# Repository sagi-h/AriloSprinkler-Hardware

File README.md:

# AriloSprinkler-Hardware
OpenSprinkler ESP32-WROOM Hardware Design variant including a Lora E22-900M30S-SX1262 and made in Kicad software.

HW features:
- 8 valve AC driver compatible with OpenSprinkler Zone Expanders
- Lora E22-900M30S-SX1262 long range transceiver (up to 30dBm)
- USB interface for debugging/flashing
- Ethernet interface (Exemplary module: https://de.aliexpress.com/item/2042562851.html?spm=a2g0s.9042311.0.0.27424c4daFHBJU)
- RF Transmitter interface (Exemplary module: https://de.aliexpress.com/item/4001119703303.html?spm=a2g0s.9042311.0.0.27424c4daFHBJU)
- Compatible with DIN rails (Used holding system: https://de.aliexpress.com/item/32827395562.html?spm=a2g0s.9042311.0.0.27424c4daFHBJU)
- Reworked current measurement with inverted precision rectifier required due to the ADC of the ESP32
- RTC
- Button switches

Tested features:
- Opensprinkler SW features work
- Lora transceiver works
- Current measurement works
- Valve control works
- Button switches work

All parts have a LCSC reference number and are at the time of writting this readme available in the JLCPCB SMT library. I have got my prototype boards produced by JLCPCB (quite inexpensive, 5 full SMT assembled and shipped PCB's for arround 75€, additionally E22 module, ESP32 and USB and SMT connectors to be added).

The compatible SW can be found in the following OpenSprinkler Firmware branch:
https://github.com/arijav/AriloSprinkler-Firmware

Note: This is a home made prototype. No guarantee of any kind is given. If you want a commercial product please order the regular OpenSprinkler official parts.

Final design (not yet produced, use at your own risk):

Prototype:

For questions send a message to:
gmail email: arijav2020

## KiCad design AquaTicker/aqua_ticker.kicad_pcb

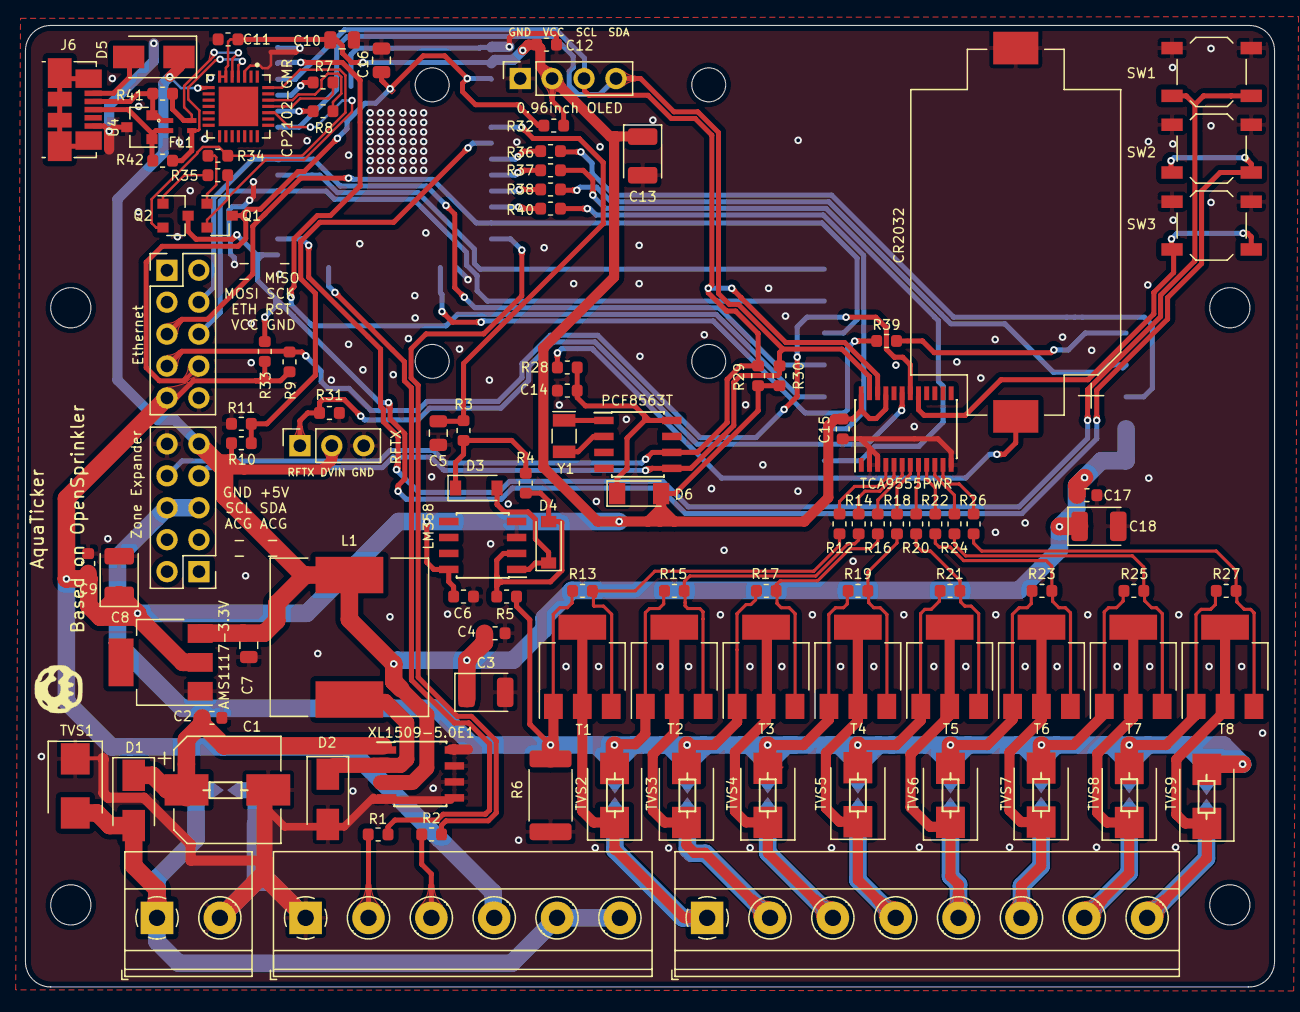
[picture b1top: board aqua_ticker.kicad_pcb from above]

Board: 2 copper layers, 99.4 x 76.5 mm, 118 parts (0 on the bottom side), 80 nets.

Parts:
BT1: CR2032; BatteryHolder_Keystone_1060_1x2032
C1: 100uF; CP_Elec_8x10
C2, C4, C6, C9, C11, C12, C14, C15, C17: 0.1u; C_0603_1608Metric
C3, C8, C13, C18: 100uF; CP_EIA-3528-21_Kemet-B
C5, C7, C10: 10u; C_0805_2012Metric
C16: 1u; C_0805_2012Metric
D1, D5: M7; D_SMA
D2: SS34; D_SMA
D3, D4: DN4148; D_SOD-123
D6: LL4148; D_MiniMELF
FL1: ACM2012-121-2P-T002; FIL_ACM2012-121-2P-T002
J1: M024MM-X; TerminalBlock_Phoenix_MKDS-1,5-2_1x02_P5.00mm_Horizontal
J2: M065MM; TerminalBlock_Phoenix_MKDS-1,5-6_1x06_P5.00mm_Horizontal
J3: RFTX; PinSocket_1x03_P2.54mm_Vertical
J4: Ethernet; PinHeader_2x05_P2.54mm_Vertical
J5: Zone Expander; PinHeader_2x05_P2.54mm_Vertical
J6: USB_B_Micro; USB_Micro-B_Molex_47346-0001
J7: M085MM-8; TerminalBlock_Phoenix_MKDS-1,5-8_1x08_P5.00mm_Horizontal
J8: 0.96inch OLED; PinSocket_1x04_P2.54mm_Vertical
L1: 68uH; L_12x12mm_H6mm
Q1, Q2: Q_NPN_BCE; SOT-23
R1, R2, R34, R35: 4K7; R_0603_1608Metric
R3: 100; R_0603_1608Metric
R4: 300K; R_0603_1608Metric
R5, R10, R11: 100K; R_0603_1608Metric
R6: 0.20; R_2512_6332Metric
R7, R8: 470; R_0603_1608Metric
R9, R28, R32: 10K; R_0603_1608Metric
R12, R14, R16, R18, R20, R22, R24, R26: 390; R_0603_1608Metric
R13, R15, R17, R19, R21, R23, R25, R27: 470K; R_0603_1608Metric
R29, R30, R31, R33: 1K; R_0603_1608Metric
R36, R37, R38, R39, R40: 22R; R_0603_1608Metric
R41, R42: 10; R_0603_1608Metric
SP1, SP2, SP3, SP4, SP5, SP6, SP7, SP8, SP9: PCB-SGAP
SW1, SW2, SW3: SW_SPST; SW_SPST_TL3342
T1, T2, T3, T4, T5, T6, T7, T8: Z0103MN5AA4; SOT-223
TVS1: 43CA; D_SMB
TVS2, TVS3, TVS4, TVS5, TVS6, TVS7, TVS8: SMBJ43CA; D_SMB
TVS9: TVSSMB; D_SMB
U1: XL1509-5.0E1; SOIC-8_3.9x4.9mm_P1.27mm
U2: LM358; SOIC-8_3.9x4.9mm_P1.27mm
U3: AMS1117-3.3V; SOT-223
U4: PSM712-LF-T7; SOT-23
U5: CP2102-GMR; QFN50P500X500X100-29N
U6: ESP32-WROOM-32D; ESP32-WROOM-32
U7: PCF8563T; SOIC-8_3.9x4.9mm_P1.27mm
U8: TCA9555PWR; TSSOP-24_4.4x7.8mm_P0.65mm
U9: E22-900M30S-SX1262
Y1: Crystal_Small; Crystal_SMD_G8-2Pin_3.2x1.5mm

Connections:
/ACRET: J5.5, J5.6, R5.1, R6.1, R13.2, R15.2, R17.2, R19.2, R21.2, R23.2, R25.2, R27.2, SP2.2, SP3.2, SP4.2, SP5.2, SP6.2, SP7.2, SP8.2, SP9.2, T1.1, T2.1, T3.1, T4.1, T5.1, T6.1, T7.1, T8.1, TVS2.2, TVS3.2, TVS4.2, TVS5.2, TVS6.2, TVS7.2, TVS8.2, TVS9.2
/BUSY: R40.2, U9.14
/COM: D1.2, J1.1, J2.5, J2.6, SP1.2, TVS1.2
/D+: FL1.2, J6.3, R42.1, U4.1
/D-: FL1.1, J6.2, R41.2, U4.2
/DADC: C5.1, R3.1, U6.6
/DIO1: R37.2, U9.13
/DIO2: R36.2, U9.8
/DM: FL1.4, R41.1, U5.5
/DP: FL1.3, R42.2, U5.4
/DSCL: J5.8, J8.3, R29.2, U6.36, U7.6, U8.22
/DSDA: J5.7, J8.4, R30.2, U6.33, U7.5, U8.23
/DTR: Q2.2, R34.2, U5.28
/DVIN: C3.1, C4.1, C7.1, C17.1, C18.1, D5.1, J3.2, J5.9, L1.2, R11.1, U1.3, U3.3, U5.8, U9.9, U9.10
/DVINSENS: R10.1, R11.2, U6.7
/ETH: J4.7, R9.2, U8.18
/GPIO0: Q2.3, R33.2, SW2.1, U6.25
/IO13: R39.1, U6.16
/IO25: R38.1, U6.10
/IO26: R40.1, U6.11
/IO32: R36.1, U6.8
/IO33: R37.1, U6.9
/MISO: J4.4, U6.31, U9.16
/MOSI: J4.5, U6.12, U9.17
/NSS_SEL: U6.30, U9.19
/P0: R12.1, U8.4
/P1: R14.1, U8.5
/P2: R16.1, U8.6
/P3: R18.1, U8.7
/P4: R20.1, U8.8
/P5: R22.1, U8.9
/P6: R24.1, U8.10
/P7: R26.1, U8.11
/RESET: U6.37, U9.15
/RFTX: J3.1, R31.1, U8.19
/RST: C16.1, J4.8, Q1.3, R32.1, U6.3
/RTS: Q1.2, R35.2, U5.24
/RXD: R8.2, U6.34
/RXEN: R39.2, U9.6
/SCK: J4.6, U6.29, U9.18
/SENS1: R1.2, U6.23
/SENS2: R2.2, U6.13
/SW1: SW1.1, U6.26
/SW3: SW3.1, U8.17
/TXD: R7.2, U6.35
/TXEN: R38.2, U9.7
/VBUS: D5.2, J6.1
/VCC: C6.1, C8.1, C9.1, C10.1, C11.1, C12.1, C13.1, C15.1, D6.2, J2.4, J4.9, J8.2, R9.1, R29.1, R30.1, R32.2, R33.1, U2.8, U3.2, U5.6, U5.7, U6.2, U8.21, U8.24
GND: BT1.2, C1.2, C2.2, C3.2, C4.2, C5.2, C6.2, C7.2, C8.2, C9.2, C10.2, C11.2, C12.2, C13.2, C14.2, C15.2, C16.2, C17.2, C18.2, D2.2, J1.2, J2.1, J3.3, J4.10, J5.10, J6.5, J8.1, R6.2, R10.2, R31.2, SP1.1, SW1.2, SW2.2, SW3.2, TVS1.1, U1.4, U1.5, U1.6, U1.7, U1.8, U2.3, U2.4, U3.1, U4.3, U5.3, U6.1, U6.15, U6.38, U6.39, U7.4, U8.2, U8.3, U8.12, U9.1, U9.2, U9.3, U9.4, U9.5, U9.11, U9.12, U9.20, U9.22
unnamed: BT1.1, R28.2
unnamed: C1.1, C2.1, D1.1, U1.1
unnamed: C14.1, D6.1, R28.1, U7.8
unnamed: D2.1, L1.1, U1.2
unnamed: D3.1, R3.2, R4.2
unnamed: D3.2, D4.1, U2.1
unnamed: D4.2, R4.1, R5.2, U2.2
unnamed: J2.2, R1.1
unnamed: J2.3, R2.1
unnamed: J7.1, SP2.1, T1.2, T1.4, TVS2.1
unnamed: J7.2, SP3.1, T2.2, T2.4, TVS3.1
unnamed: J7.3, SP4.1, T3.2, T3.4, TVS4.1
unnamed: J7.4, SP5.1, T4.2, T4.4, TVS5.1
unnamed: J7.5, SP6.1, T5.2, T5.4, TVS6.1
unnamed: J7.6, SP7.1, T6.2, T6.4, TVS7.1
unnamed: J7.7, SP8.1, T7.2, T7.4, TVS8.1
unnamed: J7.8, SP9.1, T8.2, T8.4, TVS9.1
unnamed: Q1.1, R34.1
unnamed: Q2.1, R35.1
unnamed: R7.1, U5.25
unnamed: R8.1, U5.26
unnamed: R12.2, R13.1, T1.3
unnamed: R14.2, R15.1, T2.3
unnamed: R16.2, R17.1, T3.3
unnamed: R18.2, R19.1, T4.3
unnamed: R20.2, R21.1, T5.3
unnamed: R22.2, R23.1, T6.3
unnamed: R24.2, R25.1, T7.3
unnamed: R26.2, R27.1, T8.3
unnamed: U7.1, Y1.1
unnamed: U7.2, Y1.2

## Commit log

2021-01-06 Initial AriloSprinkler HW commit
2021-04-14 kicad_plugins: remove teardrop plugin
2021-04-14 Pictures: remove Pictures forlder
2021-04-14 libraries: remove lc_kicad library
2021-04-14 libraries: use standalone E22-900M30S-SX1262 library
2021-04-14 Logos: remove Logos folder
2021-04-14 kicad: add lib table files
2021-04-14 gitignore: update with kicad files
2021-04-14 libraries: rename file
2021-05-30 AquaTicker initial commit
